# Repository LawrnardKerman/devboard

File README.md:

### devboard
this is a silly devboard with a rp2040 and battery controller, it should work with most single cell lipo batteries

there's 16MB of flash memory by default, you can just change it in the bom, the prod files are for jlcpcb pcb assembly
it *should* work as a raspberry pi pico because most of the components are the same
there's a 3.3v in and gnd connector next to the battery connector
you can just use it like any other microcontroller
basically, this is just a fun, simple microcontroller

I've been really addicted to pcb design so this project is just a practice for pcb design
hope you like it :3 

ps: like 4 weeks later i dont care about pcb design anymore
and the actually production bom doesnt have the price values just so it doesn't mess with jlcpcb's bom system

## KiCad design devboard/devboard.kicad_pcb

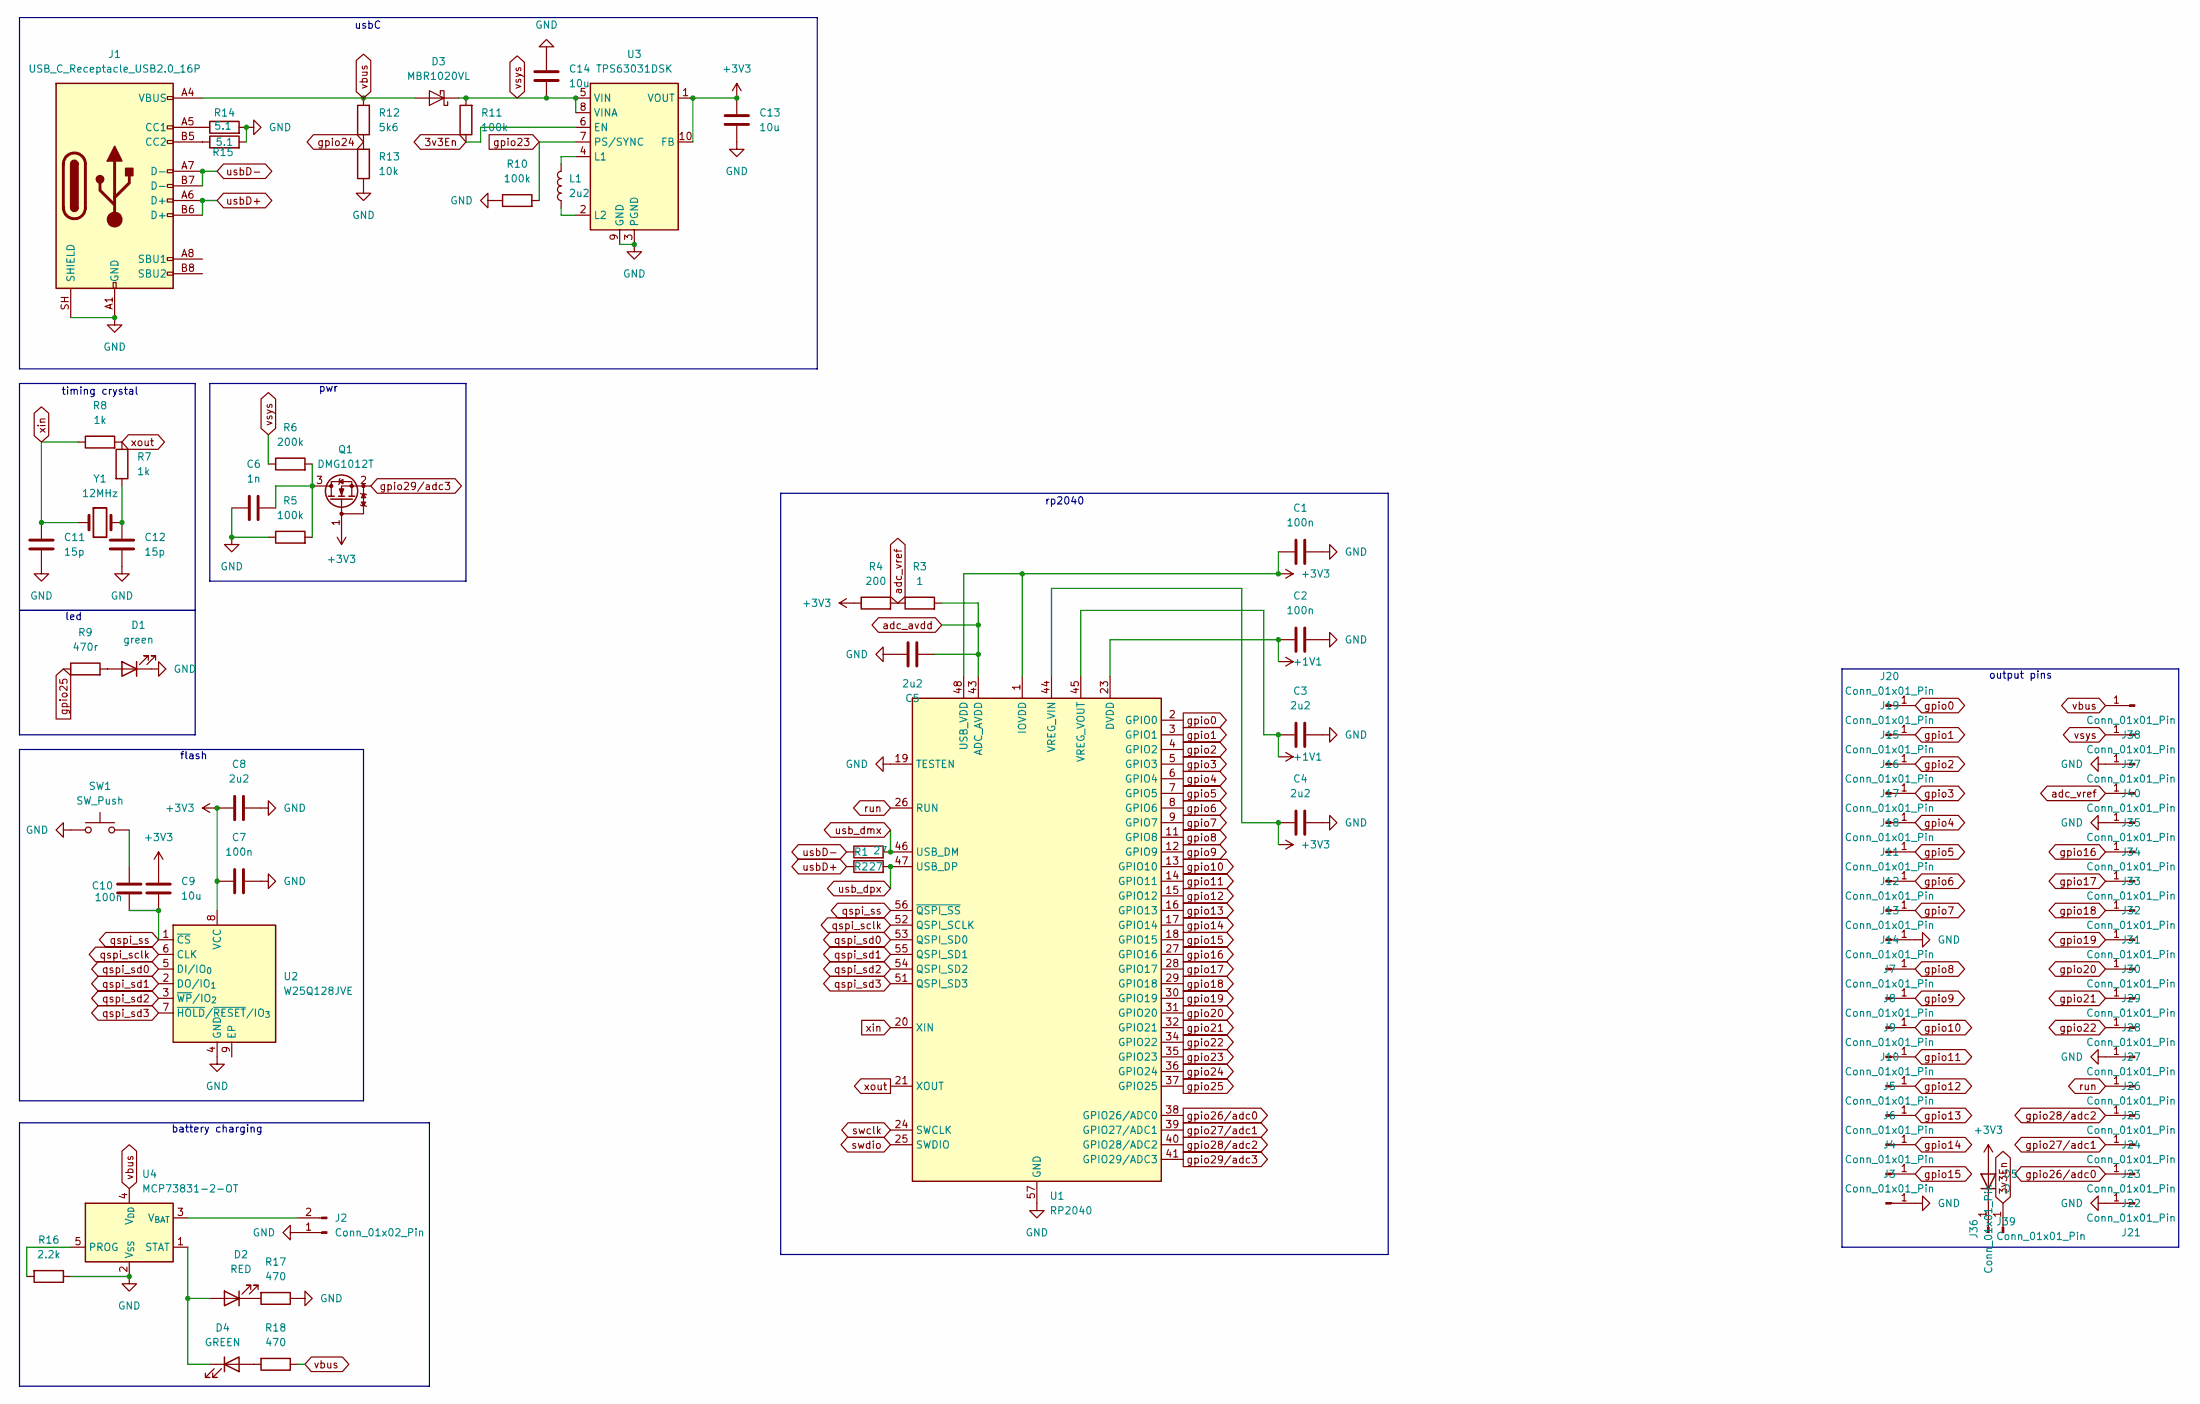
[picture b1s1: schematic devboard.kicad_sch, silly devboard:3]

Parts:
C1, C2, C7, C10: 100n; C_01005_0402Metric
C3, C4, C5, C8: 2u2; C_01005_0402Metric
C6: 1n; C_01005_0402Metric
C9, C13, C14: 10u; C_01005_0402Metric
C11, C12: 15p; C_01005_0402Metric
D1: green; LED_0201_0603Metric
D2: RED; LED_0201_0603Metric
D3: MBR1020VL; D_SOD-123F
D4: GREEN; LED_0201_0603Metric
D5: D; D_01005_0402Metric
J1: USB_C_Receptacle_USB2.0_16P; USB_C_Receptacle_G-Switch_GT-USB-7010ASV
J2: Conn_01x02_Pin; JST_PH_S2B-PH-K_1x02_P2.00mm_Horizontal
J3, J4, J5, J6, J7, J8, J9, J10, J11, J12, J13, J14, J15, J16, J17, J18, J19, J20, J21, J22, J23, J24, J25, J26, J27, J28, J29, J30, J31, J32, J33, J34, J35, J36, J37, J38, J39, J40: Conn_01x01_Pin; edgeConnectorPad
L1: 2u2; L_01005_0402Metric
Q1: DMG1012T; SOT-523
R1, R2: 27; R_01005_0402Metric
R3: 1; R_01005_0402Metric
R4: 200; R_01005_0402Metric
R5, R10, R11: 100k; R_01005_0402Metric
R6: 200k; R_01005_0402Metric
R7, R8: 1k; R_01005_0402Metric
R9: 470r; R_01005_0402Metric
R12: 5k6; R_01005_0402Metric
R13: 10k; R_01005_0402Metric
R14, R15: 5.1; R_01005_0402Metric
R16: 2.2k; R_01005_0402Metric
R17, R18: 470; R_01005_0402Metric
SW1: SW_Push; SW_Push_1P1T_NO_CK_KMR2
U1: RP2040; QFN-56-1EP_7x7mm_P0.4mm_EP3.2x3.2mm
U2: W25Q128JVE; WSON-8-1EP_8x6mm_P1.27mm_EP3.4x4.3mm
U3: TPS63031DSK; WSON-10-1EP_2.5x2.5mm_P0.5mm_EP1.2x2mm_ThermalVias
U4: MCP73831-2-OT; SOT-23-5
Y1: 12MHz; Crystal_SMD_5032-2Pin_5.0x3.2mm

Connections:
3v3En: J36.1 (Pin_1_1), R11.1, U3.6 (EN)
+1V1: C2.1, C3.1, U1.23 (DVDD), U1.45 (VREG_VOUT), U1.50 (DVDD)
+3V3: C1.1, C4.1, C7.1, C8.1, C9.2, C13.1, D5.2 (A), Q1.1 (G), R4.1, U1.1 (IOVDD), U1.10 (IOVDD), U1.22 (IOVDD), U1.33 (IOVDD), U1.42 (IOVDD), U1.44 (VREG_VIN), U1.48 (USB_VDD), U1.49 (IOVDD), U2.8 (VCC), U3.1 (VOUT), U3.10 (FB)
GND: C1.2, C2.2, C3.2, C4.2, C5.2, C6.1, C7.2, C8.2, C11.2, C12.2, C13.2, C14.1, D1.1 (K), J1.A1 (GND), J1.A12 (GND), J1.B1 (GND), J1.B12 (GND), J1.SH (SHIELD), J2.1, J3.1 (Pin_1_1), J13.1 (Pin_1_1), J21.1 (Pin_1_1), J26.1 (Pin_1_1), J34.1 (Pin_1_1), J40.1 (Pin_1_1), R5.1, R10.1, R13.1, R14.2, R15.2, R16.1, R17.1, SW1.1, U1.19 (TESTEN), U1.57 (GND), U2.4 (GND), U3.3 (PGND), U3.9 (GND), U3.11 (PGND), U4.2 (V_{SS})
unnamed: C10.2, SW1.2
unnamed: C12.1, R7.2, Y1.2
unnamed: D1.2 (A), R9.2
unnamed: D2.2 (A), D4.1 (K), U4.1 (STAT)
unnamed: D2.1 (K), R17.2
unnamed: D4.2 (A), R18.2
unnamed: D5.1 (K), J39.1 (Pin_1_1)
unnamed: J1.A5 (CC1), R14.1
unnamed: J1.B5 (CC2), R15.1
unnamed: J2.2, U4.3 (V_{BAT})
unnamed: C6.2, Q1.3 (D), R5.2, R6.2
unnamed: L1.2, U3.4 (L1)
unnamed: L1.1, U3.2 (L2)
unnamed: R16.2, U4.5 (PROG)
adc_avdd: C5.1, R3.2, U1.43 (ADC_AVDD)
adc_vref: J35.1 (Pin_1_1), R3.1, R4.2
gpio0: J20.1 (Pin_1_1), U1.2 (GPIO0)
gpio1: J19.1 (Pin_1_1), U1.3 (GPIO1)
gpio2: J15.1 (Pin_1_1), U1.4 (GPIO2)
gpio3: J16.1 (Pin_1_1), U1.5 (GPIO3)
gpio4: J17.1 (Pin_1_1), U1.6 (GPIO4)
gpio5: J18.1 (Pin_1_1), U1.7 (GPIO5)
gpio6: J11.1 (Pin_1_1), U1.8 (GPIO6)
gpio7: J12.1 (Pin_1_1), U1.9 (GPIO7)
gpio8: J14.1 (Pin_1_1), U1.11 (GPIO8)
gpio9: J7.1 (Pin_1_1), U1.12 (GPIO9)
gpio10: J8.1 (Pin_1_1), U1.13 (GPIO10)
gpio11: J9.1 (Pin_1_1), U1.14 (GPIO11)
gpio12: J10.1 (Pin_1_1), U1.15 (GPIO12)
gpio13: J5.1 (Pin_1_1), U1.16 (GPIO13)
gpio14: J6.1 (Pin_1_1), U1.17 (GPIO14)
gpio15: J4.1 (Pin_1_1), U1.18 (GPIO15)
gpio16: J33.1 (Pin_1_1), U1.27 (GPIO16)
gpio17: J32.1 (Pin_1_1), U1.28 (GPIO17)
gpio18: J31.1 (Pin_1_1), U1.29 (GPIO18)
gpio19: J30.1 (Pin_1_1), U1.30 (GPIO19)
gpio20: J29.1 (Pin_1_1), U1.31 (GPIO20)
gpio21: J28.1 (Pin_1_1), U1.32 (GPIO21)
gpio22: J27.1 (Pin_1_1), U1.34 (GPIO22)
gpio23: R10.2, U1.35 (GPIO23), U3.7 (PS/SYNC)
gpio24: R12.1, R13.2, U1.36 (GPIO24)
gpio25: R9.1, U1.37 (GPIO25)
gpio26/adc0: J22.1 (Pin_1_1), U1.38 (GPIO26/ADC0)
gpio27/adc1: J23.1 (Pin_1_1), U1.39 (GPIO27/ADC1)
gpio28/adc2: J24.1 (Pin_1_1), U1.40 (GPIO28/ADC2)
gpio29/adc3: Q1.2 (S), U1.41 (GPIO29/ADC3)
qspi_sclk: U1.52 (QSPI_SCLK), U2.6 (CLK)
qspi_sd0: U1.53 (QSPI_SD0), U2.5 (DI/IO_{0})
qspi_sd1: U1.55 (QSPI_SD1), U2.2 (DO/IO_{1})
qspi_sd2: U1.54 (QSPI_SD2), U2.3 (~WP/IO_{2})
qspi_sd3: U1.51 (QSPI_SD3), U2.7 (~HOLD/~RESET/IO_{3})
qspi_ss: C9.1, C10.1, U1.56 (~QSPI_SS), U2.1 (~CS)
run: J25.1 (Pin_1_1), U1.26 (RUN)
swclk: U1.24 (SWCLK)
swdio: U1.25 (SWDIO)
usbD+: J1.A6 (D+), J1.B6 (D+), R2.1
usbD-: J1.A7 (D-), J1.B7 (D-), R1.1
usb_dmx: R1.2, U1.46 (USB_DM)
usb_dpx: R2.2, U1.47 (USB_DP)
vbus: D3.2 (A), J1.A4 (VBUS), J1.A9 (VBUS), J1.B4 (VBUS), J1.B9 (VBUS), J38.1 (Pin_1_1), R12.2, R18.1, U4.4 (V_{DD})
vsys: C14.2, D3.1 (K), J37.1 (Pin_1_1), R6.1, R11.2, U3.5 (VIN), U3.8 (VINA)
xin: C11.1, R8.1, U1.20 (XIN), Y1.1
xout: R7.1, R8.2, U1.21 (XOUT)

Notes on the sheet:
usbC
pwr
battery charging
output pins
flash
timing crystal
led
rp2040

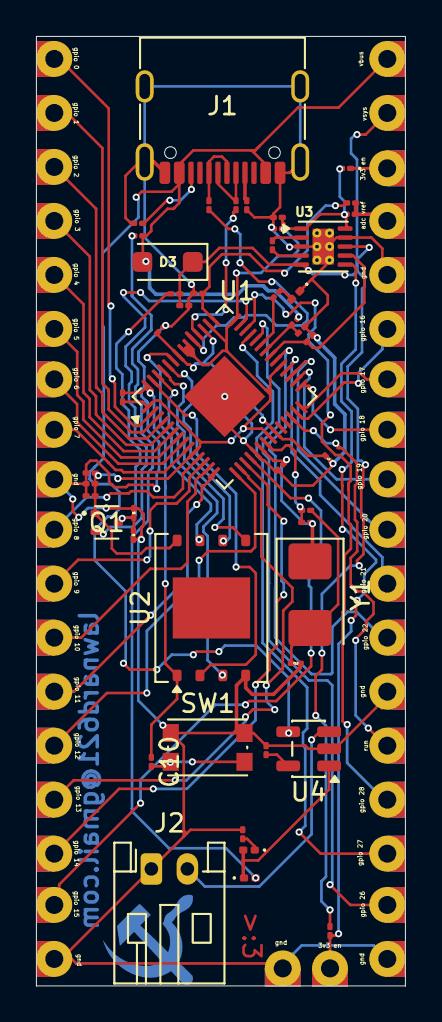
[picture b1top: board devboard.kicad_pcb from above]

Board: 2 copper layers, 20.5 x 52.8 mm, 85 parts (0 on the bottom side), 65 nets.

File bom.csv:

Designator,Footprint,Quantity,Value,LCSC Part #,per unit price($),total price($),note,
"C1, C10, C2, C7",1005,4,100n,C1525,$0.0045,$0.02,,
"C11, C12",1005,2,15p,C1548,$0.0038,$0.01,,
"C13, C14, C9",1005,3,10u,C15525,$0.0256,$0.08,,
"C3, C4, C5, C8",1005,5,2u2,C12530,$0.0053,$0.03,,
C6,1005,1,1n,C1523,$0.0042,$0.01,,
"D1, D4",201,2,green,C2290,$0.0122,$0.02,,
D2,201,1,RED,C2286,$0.0122,$0.01,,
D3,D_SOD-123F,1,MBR1020VL,C49231015,$0.0955,$0.10,,
D5,1005,1,D,C94366,$0.1147,$8.72,note: min amount on jlc pcb is 78,extended
Q1,SOT-523,1,DMG1012T,C2830301,$0.0371,$0.04,,
"R1, R2",1005,2,27,C174257,$0.0007,$0.01,,
"R10, R11, R5",1005,3,100k,C25741,$0.0024,$0.01,,
R12,1005,1,5k6,C174239,$0.0017,$0.01,,
R13,1005,1,10k,C25744,$0.0034,$0.01,,
"R14, R15",1005,2,5.1,C25128,$0.0034,$8.77,note: min amount on jlc is 2578,extended
R16,1005,1,2.2k,C25879,$0.0013,$0.01,,
R3,1005,1,1,C22369188,$0.0011,$0.01,,
R4,1005,1,200,C25087,$0.0029,$0.01,,
R6,1005,1,200k,C25764,$0.0018,$0.01,,
"R7, R8,R17, R18",1005,2,1k,C11702,$0.0018,$0.01,,
R9,1005,1,470r,C25117,$0.0027,$0.01,,
SW1,SW_Push_1P1T_NO_CK_KMR2,1,SW_Push,C72443,$0.6503,$0.65,,extended
U1,QFN-56-1EP_7x7mm_P0.4mm_EP3.2x3.2mm,1,RP2040,C2040,$0.9884,$0.99,,extended
U2,WSON-8-1EP_8x6mm_P1.27mm_EP3.4x4.3mm,1,W25Q128JVE,C2456297,$4.0886,$4.09,16MB,extended
U3,WSON-10-1EP_2.5x2.5mm_P0.5mm_EP1.2x2mm_ThermalVias,1,TPS63031DSK,C15516,$1.0291,$1.03,,extended
U4,SOT-23-5,1,MCP73831-2-OT,C14879 ,$1.3006,$1.30,,extended
Y1,Crystal_SMD_5032-2Pin_5.0x3.2mm,1,12MHz,C295065,$0.3489,$0.35,,extended
J1,USB_C_Receptacle_G-Switch_GT-USB-7010ASV,1,USB_C_Receptacle_USB2.0_16P,C2927037,$0.1441,$0.14,,extended
L1,1005,1,2u2,C84472,$0.0174,$0.02,,extended
total component cost,,,,,,$26.48,,
pcb cost,,,,,,$5.10,5 pcbs,
pcba cost,,,,,,$80.36,includes components(2 boards),
grant total,,,,,,$85.46,not counting taxes & shipping,
